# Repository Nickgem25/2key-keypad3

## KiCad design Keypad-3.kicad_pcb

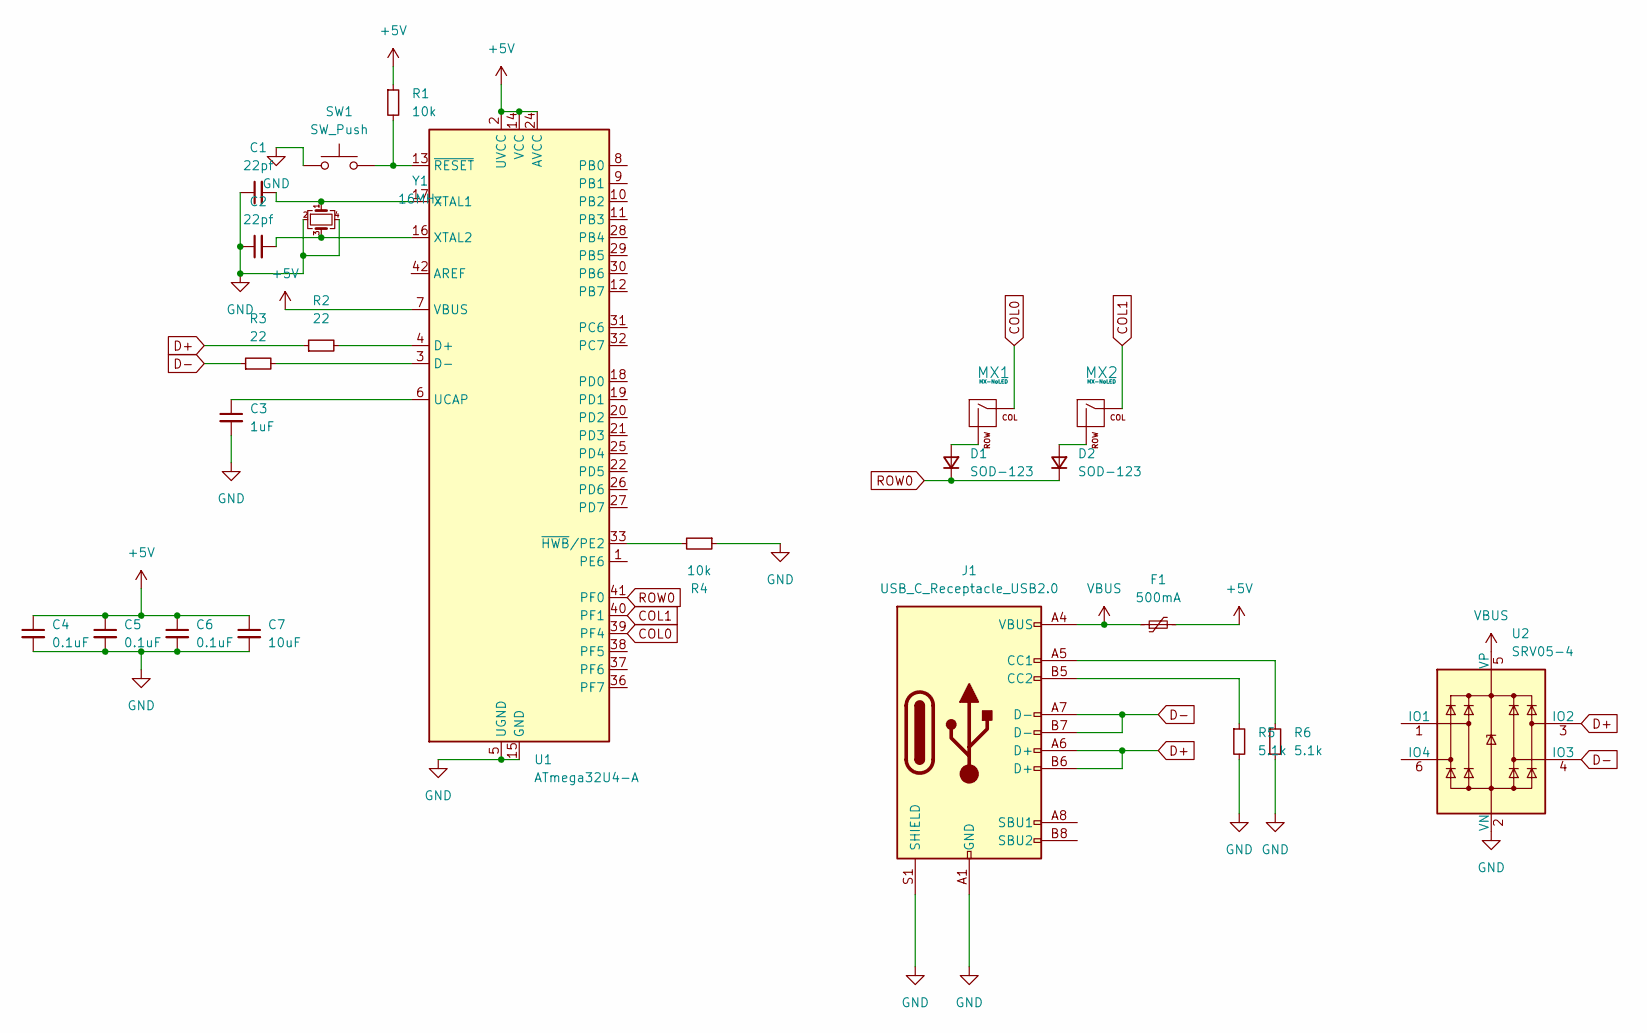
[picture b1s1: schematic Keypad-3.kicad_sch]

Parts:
C1: 22pf; R_0805_2012Metric
C2: 22pf; C_0805_2012Metric
C3: 1uF; C_0805_2012Metric
C4, C5, C6: 0.1uF; C_0805_2012Metric
C7: 10uF; C_0805_2012Metric
D1, D2: SOD-123; D_SOD-123
F1: 500mA; Fuse_1206_3216Metric
J1: USB_C_Receptacle_USB2.0; USB_C_Receptacle_HRO_TYPE-C-31-M-12
MX1, MX2: MX-NoLED; MX-1U-NoLED
R1, R4: 10k; R_0805_2012Metric
R2, R3: 22; R_0805_2012Metric
R5, R6: 5.1k; R_0805_2012Metric
SW1: SW_Push; SKQG-1155865
U1: ATmega32U4-A; TQFP-44_10x10mm_P0.8mm
U2: SRV05-4; SOT-23-6-routable
Y1: 16MHz; Crystal_SMD_3225-4Pin_3.2x2.5mm

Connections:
+5V: C4.1, C5.1, C6.1, C7.1, F1.2, R1.1, U1.2 (UVCC), U1.7 (VBUS), U1.14 (VCC), U1.24 (AVCC), U1.34 (VCC), U1.44 (AVCC)
COL0: MX1.1 (COL), U1.39 (PF4)
COL1: MX2.1 (COL), U1.40 (PF1)
D+: J1.A6 (D+), J1.B6 (D+), R2.1, U2.3 (IO2)
D-: J1.A7 (D-), J1.B7 (D-), R3.1, U2.4 (IO3)
GND: C1.1, C2.1, C3.2, C4.2, C5.2, C6.2, C7.2, J1.A1 (GND), J1.A12 (GND), J1.B1 (GND), J1.B12 (GND), J1.S1 (SHIELD), R4.1, R5.2, R6.2, SW1.1, U1.5 (UGND), U1.15 (GND), U1.23 (GND), U1.35 (GND), U1.43 (GND), U2.2 (VN), Y1.2, Y1.4
unnamed: C1.2, U1.17 (XTAL1), Y1.1
unnamed: C2.2, U1.16 (XTAL2), Y1.3
unnamed: C3.1, U1.6 (UCAP)
unnamed: D1.2 (A), MX1.2 (ROW)
unnamed: D2.2 (A), MX2.2 (ROW)
unnamed: J1.A5 (CC1), R6.1
unnamed: J1.B5 (CC2), R5.1
unnamed: R1.2, SW1.2, U1.13 (~RESET)
unnamed: R2.2, U1.4 (D+)
unnamed: R3.2, U1.3 (D-)
unnamed: R4.2, U1.33 (~HWB/PE2)
ROW0: D1.1 (K), D2.1 (K), U1.41 (PF0)
VBUS: F1.1, J1.A4 (VBUS), J1.A9 (VBUS), J1.B4 (VBUS), J1.B9 (VBUS), U2.5 (VP)

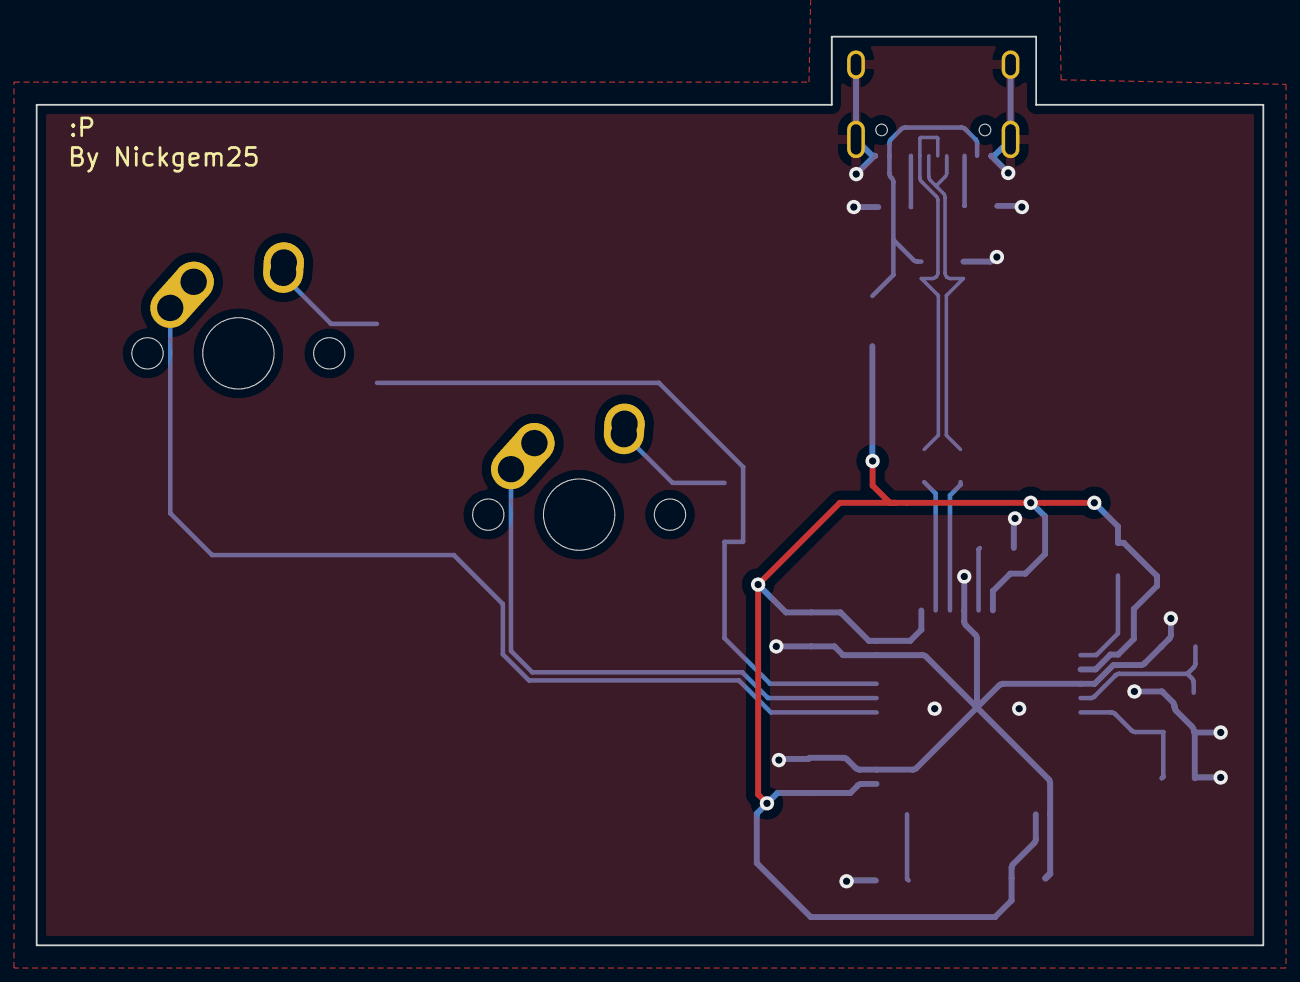
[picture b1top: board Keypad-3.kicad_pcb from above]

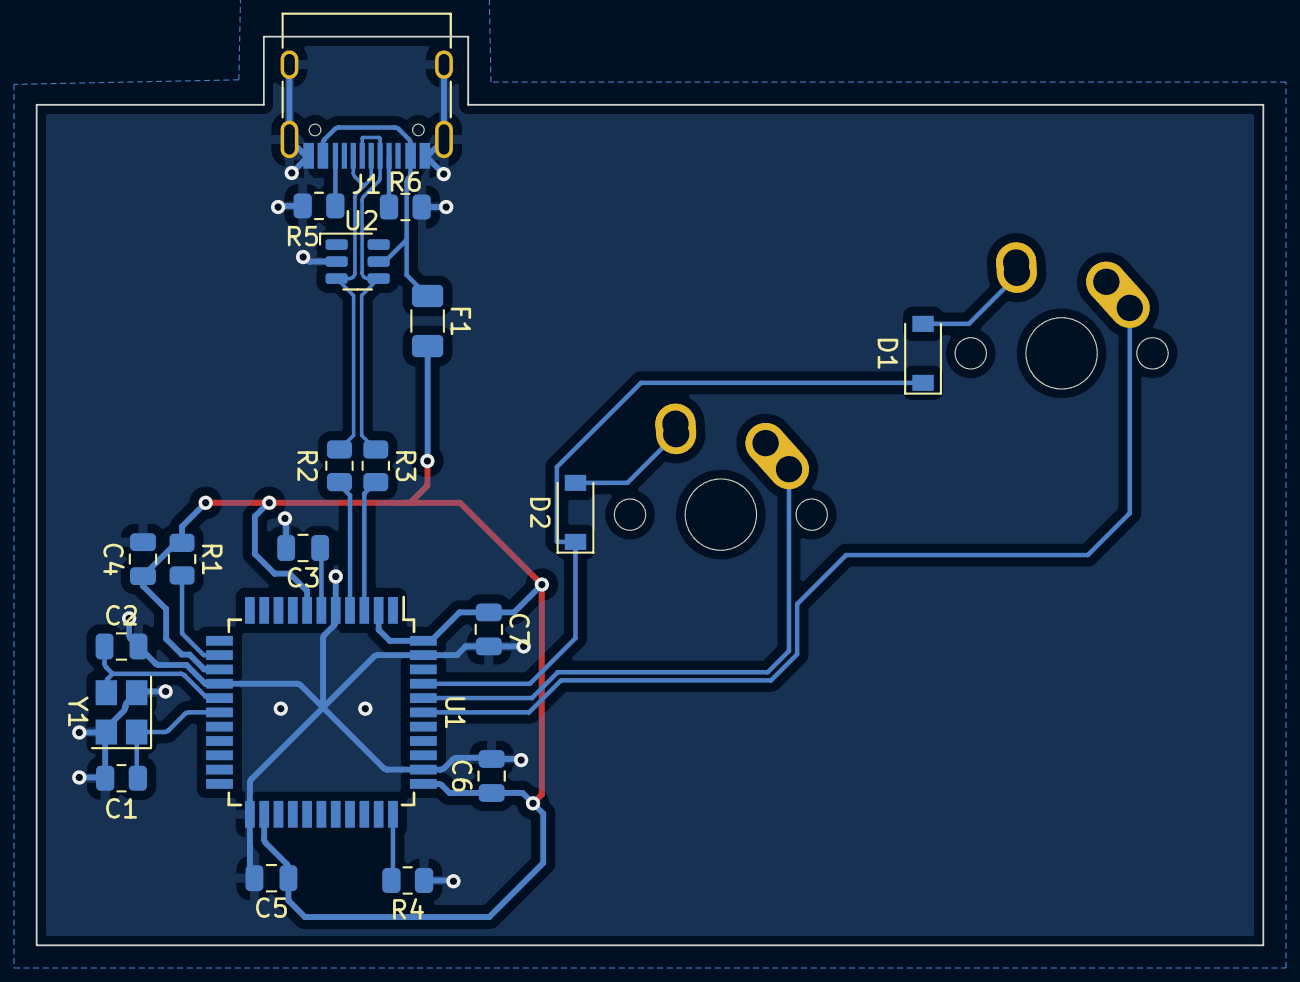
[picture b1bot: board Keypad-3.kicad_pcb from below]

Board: 2 copper layers, 68.6 x 50.8 mm, 22 parts (20 on the bottom side), 19 nets.

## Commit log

2022-08-06 Initialize project
2022-08-06 added submodules & other stuff
    added some submodules duh
2022-08-06 Schematic & footprint binding
    Schematic & footprint binding are finish
    Finally!
2022-08-07 Finished first board design
    route is very messy, will fix soon.
2022-08-09 Fixed usb c tracing
    I made the usb-c traces straight and re arranged the board to a different layout
2022-08-09 re-arranged some tracings
    Better tracing arrangement
2022-08-09 Made the gerber files
    :D
2022-09-04 Final Design (for real this time I think)
    Removed the switch.
